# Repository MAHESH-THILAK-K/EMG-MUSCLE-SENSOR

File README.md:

Below is a **README-style documentation** written in the **same format, tone, and structure** as your Stellar Vision V1 README, but **customized for your `_PRO` / schematic project file** (KiCad `.kicad_pro`, `.kicad_sch`, PCB context).
You can use this as **README.md inside the Circuits / Schematics folder** or alongside the `.kicad_pro` file.

---

# Muscle Sensor (EMG) – Hardware Schematic Project

**Project Type:** Analog Signal Conditioning PCB
**Design Tool:** KiCad
**Project File:** `Muscle sensor.kicad_pro`

---

## 📌 Project Overview

**Muscle Sensor (EMG) Schematic Project** is a precision **analog front-end design** intended for acquiring, amplifying, filtering, and conditioning **electromyography (EMG) signals** from human muscles.
This project focuses on **low-noise PCB design practices**, adjustable gain control, and microcontroller-compatible analog output.

The schematic is designed for **educational, research, and embedded biomedical applications**, ensuring signal integrity for very low-amplitude bioelectric signals.

---

## ✨ Key Features

🟠 **Differential EMG Input**
• Supports 3-electrode EMG configuration
• High input impedance for accurate signal pickup

🔍 **Precision Amplification**
• Instrumentation / op-amp based differential amplifier
• High CMRR for power-line noise rejection

🎚 **Adjustable Gain Control**
• Multi-turn 3296W trimmer potentiometer
• Easy calibration for different muscle strengths

🎛 **Active Filtering Stage**
• High-pass filter for DC offset & motion artifact removal
• Low-pass filter for high-frequency noise suppression

🔊 **Conditioned Analog Output**
• Clean, single-ended voltage output
• Direct ADC compatibility (ESP32, Arduino, STM32)

🔌 **Stable Power Architecture**
• Proper decoupling and grounding
• Low-noise operation for biomedical signals

---

## 🛠 Technical Specifications

| Parameter       | Specification              |
| --------------- | -------------------------- |
| Signal Type     | EMG (Electromyography)     |
| Input Range     | Microvolt to millivolt     |
| Amplifier Type  | Precision Op-Amp           |
| Gain Control    | 3296W multi-turn trimmer   |
| Filtering       | Active HPF + LPF           |
| Output Type     | Analog (ADC compatible)    |
| PCB Design Tool | KiCad                      |
| Project File    | `.kicad_pro`, `.kicad_sch` |

---

## 📦 Project File Structure

```
Muscle_Sensor_EMG/
├── Muscle sensor.kicad_pro     # KiCad project file
├── Muscle sensor.kicad_sch     # Schematic design
├── Muscle sensor.kicad_pcb     # PCB layout (if available)
├── BOM/                        # Bill of Materials
├── PDF/                        # Exported schematic PDFs
├── README.md                   # This documentation
```

---

## ⚙️ Functional Block Description

### 1️⃣ Electrode Input Interface

• Three-electrode EMG input (Differential + Reference)
• Designed for minimal noise pickup
• Short, symmetric routing recommended

### 2️⃣ Differential Amplifier Stage

• Amplifies weak EMG signals
• Rejects common-mode noise (50/60 Hz)
• Feedback components placed close to op-amp

### 3️⃣ Gain Adjustment Network

• Trimmer potentiometer controls amplification level
• Enables per-user or per-muscle calibration

### 4️⃣ Active Filter Section

• High-pass filtering removes baseline drift
• Low-pass filtering reduces EMI and noise

### 5️⃣ Output Conditioning

• Provides stable voltage output
• Protects MCU ADC input

### 6️⃣ Power & Grounding

• Dedicated decoupling capacitors
• Continuous analog ground reference

---

## 🚀 Getting Started

### Prerequisites

* KiCad (v6 or later recommended)
* Basic understanding of analog electronics
* Optional: Microcontroller for signal testing

### Usage

1. Open `Muscle sensor.kicad_pro` in KiCad
2. Review schematic connections and values
3. Adjust gain resistor / trimmer values if required
4. Export schematic PDF or proceed to PCB layout
5. Fabricate PCB and test with EMG electrodes

---

## 🧪 Testing & Calibration

* Power the circuit using a regulated DC supply
* Adjust trimmer while observing output via oscilloscope
* Verify signal stability before MCU connection
* Ensure proper grounding during human testing

⚠ **Note:** This circuit is for **educational and research purposes only**. It is not a certified medical device.

---

## 📚 Documentation

* Schematic PDF – Visual circuit overview
* BOM – Component values and packages
* PCB Layout (if available) – Manufacturing ready
  
---

## 📄 License

This project is licensed under the **PolyForm Noncommercial License 1.0.0**.
Commercial use is **not permitted**.

**Copyright © 2025
MAHESH THILAK K**
---

## 👨‍💻 Author

**Mahesh Thilak K**
Bachelor of Engineering – Electronics & Communication Engineering

**Design Focus:**
Analog Signal Processing • Biomedical Electronics • Embedded Systems

---

## 🤝 Contributing

This is a personal academic project.
Suggestions, improvements, and feedback are welcome, provided all usage complies with the noncommercial license.

---

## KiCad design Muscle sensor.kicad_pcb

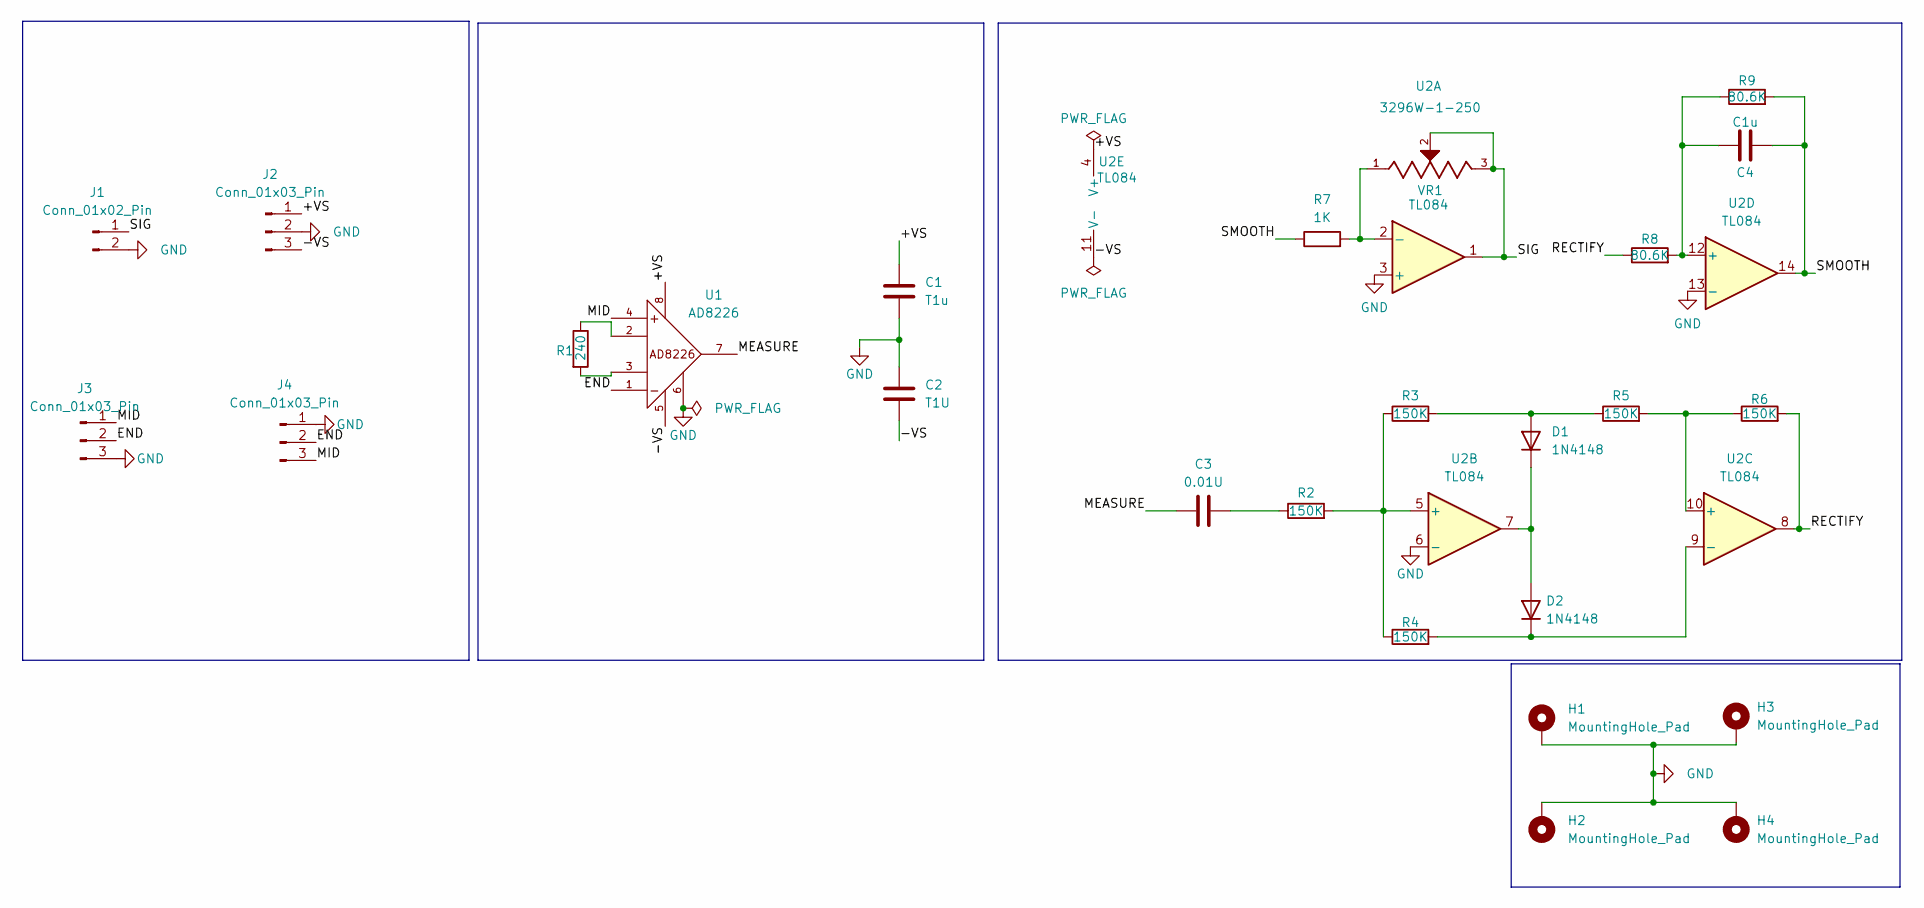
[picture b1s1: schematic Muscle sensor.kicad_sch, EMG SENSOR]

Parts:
C1: T1u; C_Radial_D5.0mm_H7.0mm_P2.00mm
C2: T1U; C_Radial_D5.0mm_H7.0mm_P2.00mm
C3: 0.01U; C_Radial_D5.0mm_H7.0mm_P2.00mm
C4: C1u; C_Radial_D5.0mm_H7.0mm_P2.00mm
D1, D2: 1N4148; D_DO-35_SOD27_P7.62mm_Horizontal
H1, H2, H3, H4: MountingHole_Pad; MountingHole_2.2mm_M2_Pad_Via
J1: Conn_01x02_Pin; JWT_A3963_1x02_P3.96mm_Vertical
J2, J3, J4: Conn_01x03_Pin; FanPinHeader_1x03_P2.54mm_Vertical
R1: 240; R_2010_5025Metric_Pad1.40x2.65mm_HandSolder
R2, R3, R4, R5, R6: 150K; R_2010_5025Metric_Pad1.40x2.65mm_HandSolder
R7: 1K; R_2010_5025Metric_Pad1.40x2.65mm_HandSolder
R8, R9: 80.6K; R_2010_5025Metric_Pad1.40x2.65mm_HandSolder
U1: AD8226; AD8286
U2: TL084; N14
VR1: 3296W-1-250; TRIM; PARTREV 05/16

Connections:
/+VS: C1.2, J2.1, U1.8, U2.4 (V+)
/-VS: C2.1, J2.3, U1.5, U2.11 (V-)
/END: J3.2, J4.2, U1.1
/MEASURE: C3.1, U1.7
/MID: J3.1, J4.3, U1.4
/RECTIFY: R6.2, R8.1, U2.8
/SIG: J1.1, U2.1, VR1.2, VR1.3
/SMOOTH: C4.2, R7.1, R9.2, U2.14
GND: C1.1, C2.2, H1.1, H2.1, H3.1, H4.1, J1.2, J2.2, J3.3, J4.1, U1.6, U2.3 (+), U2.6 (-), U2.13 (-)
unnamed: C3.2, R2.1
unnamed: D1.2 (A), R3.2, R5.1
unnamed: D1.1 (K), D2.2 (A), U2.7
unnamed: D2.1 (K), R4.2, U2.9 (-)
unnamed: R1.1, U1.2
unnamed: R1.2, U1.3
unnamed: R7.2, U2.2 (-), VR1.1
unnamed: R2.2, R3.1, R4.1, U2.5 (+)
unnamed: R5.2, R6.1, U2.10 (+)
unnamed: C4.1, R8.2, R9.1, U2.12 (+)

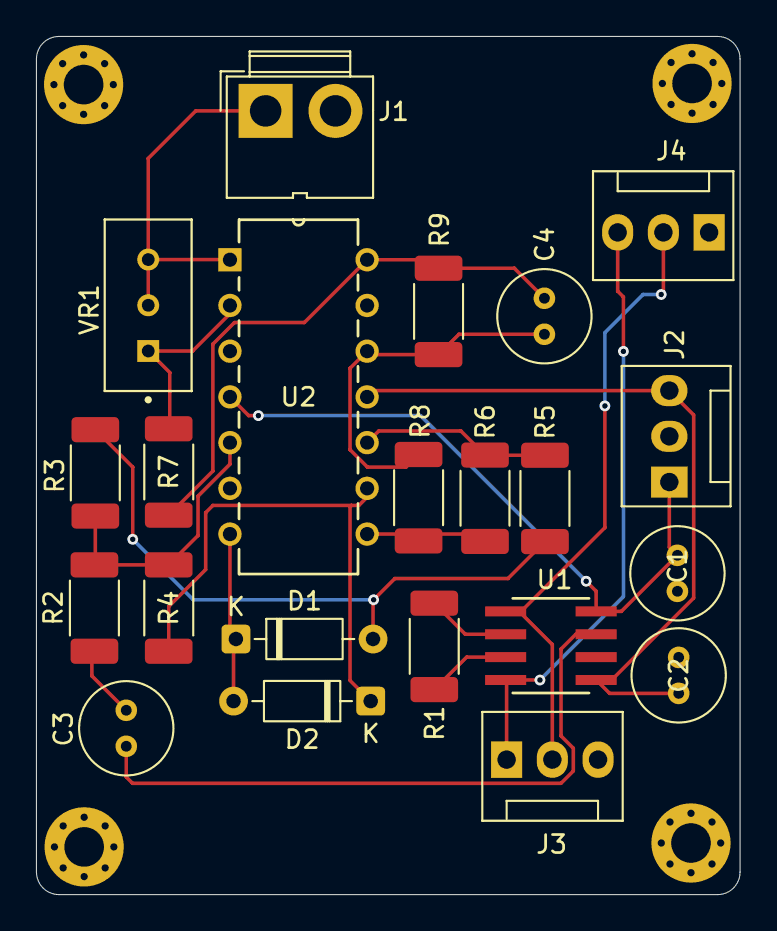
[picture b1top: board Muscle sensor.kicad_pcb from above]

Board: 2 copper layers, 39.1 x 47.7 mm, 26 parts (0 on the bottom side), 19 nets.

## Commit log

2026-01-22 Create README for Muscle Sensor EMG project
    Added detailed README documentation for the Muscle Sensor (EMG) hardware schematic project, including project overview, key features, specifications, file structure, and usage instructions.
